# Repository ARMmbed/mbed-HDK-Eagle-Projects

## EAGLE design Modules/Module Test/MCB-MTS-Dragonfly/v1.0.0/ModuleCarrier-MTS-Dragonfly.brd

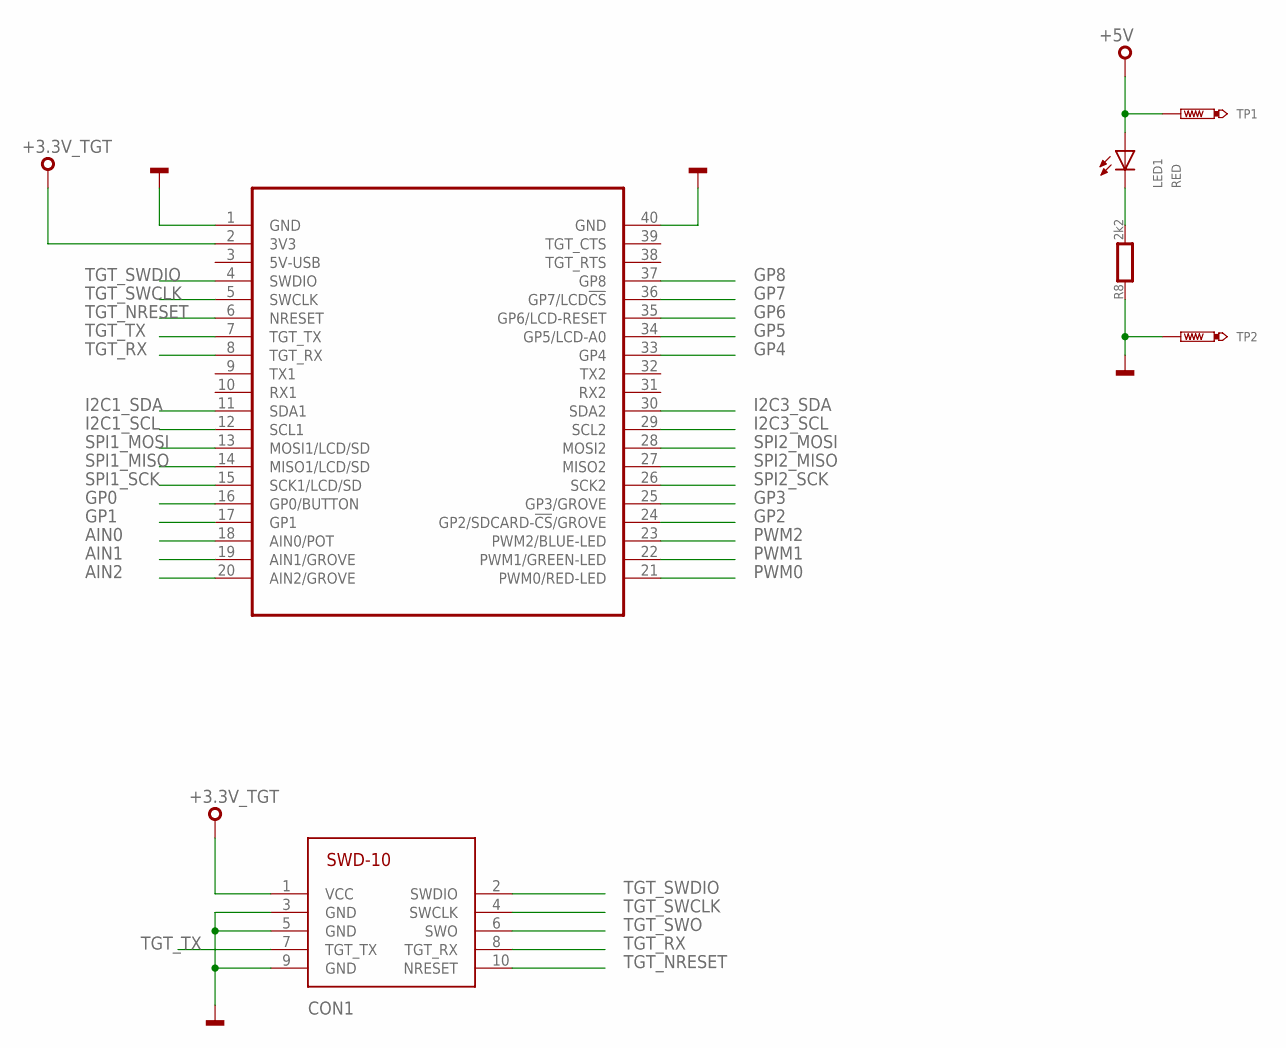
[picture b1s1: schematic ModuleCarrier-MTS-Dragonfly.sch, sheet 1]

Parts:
CON1: SWD-10/TC2050_SMD; FTSH-105-02
LED1: RED; CHIPLED_0603
MOD2: MODULE_DAUGHTER
R8: 2k2; 0603
TP1, TP2: TEST-POINT-50R-PTH; TP50-PTH

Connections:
+3.3V_TGT: CON1.1 (VCC), MOD2.2 (3V3)
+5V: LED1.A, TP1.TP; also elsewhere on the board
AIN0: MOD2.18 (AIN0/POT); also elsewhere on the board
AIN1: MOD2.19 (AIN1/GROVE); also elsewhere on the board
AIN2: MOD2.20 (AIN2/GROVE); also elsewhere on the board
GND: CON1.3 (GND), CON1.5 (GND), CON1.9 (GND), MOD2.1 (GND), MOD2.40 (GND), R8.1, TP2.TP; also elsewhere on the board
GP0: MOD2.16 (GP0/BUTTON); also elsewhere on the board
GP1: MOD2.17 (GP1); also elsewhere on the board
GP2: MOD2.24 (GP2/SDCARD-!CS!/GROVE); also elsewhere on the board
GP3: MOD2.25 (GP3/GROVE); also elsewhere on the board
GP4: MOD2.33 (GP4); also elsewhere on the board
GP5: MOD2.34 (GP5/LCD-A0); also elsewhere on the board
GP6: MOD2.35 (GP6/LCD-RESET); also elsewhere on the board
GP7: MOD2.36 (GP7/LCD!CS); also elsewhere on the board
GP8: MOD2.37 (GP8); also elsewhere on the board
I2C1_SCL: MOD2.12 (SCL1); also elsewhere on the board
I2C1_SDA: MOD2.11 (SDA1); also elsewhere on the board
I2C3_SCL: MOD2.29 (SCL2); also elsewhere on the board
I2C3_SDA: MOD2.30 (SDA2); also elsewhere on the board
PA_1: LED1.C, R8.2
PWM0: MOD2.21 (PWM0/RED-LED); also elsewhere on the board
PWM1: MOD2.22 (PWM1/GREEN-LED); also elsewhere on the board
PWM2: MOD2.23 (PWM2/BLUE-LED); also elsewhere on the board
SPI1_MISO: MOD2.14 (MISO1/LCD/SD); also elsewhere on the board
SPI1_MOSI: MOD2.13 (MOSI1/LCD/SD); also elsewhere on the board
SPI1_SCK: MOD2.15 (SCK1/LCD/SD); also elsewhere on the board
SPI2_MISO: MOD2.27 (MISO2); also elsewhere on the board
SPI2_MOSI: MOD2.28 (MOSI2); also elsewhere on the board
SPI2_SCK: MOD2.26 (SCK2); also elsewhere on the board
TGT_NRESET: CON1.10 (NRESET), MOD2.6 (NRESET); also elsewhere on the board
TGT_RX: CON1.8 (TGT_RX), MOD2.8 (TGT_RX); also elsewhere on the board
TGT_SWCLK: CON1.4 (SWCLK), MOD2.5 (SWCLK); also elsewhere on the board
TGT_SWDIO: CON1.2 (SWDIO), MOD2.4 (SWDIO); also elsewhere on the board
TGT_SWO: CON1.6 (SWO); also elsewhere on the board
TGT_TX: CON1.7 (TGT_TX), MOD2.7 (TGT_TX); also elsewhere on the board

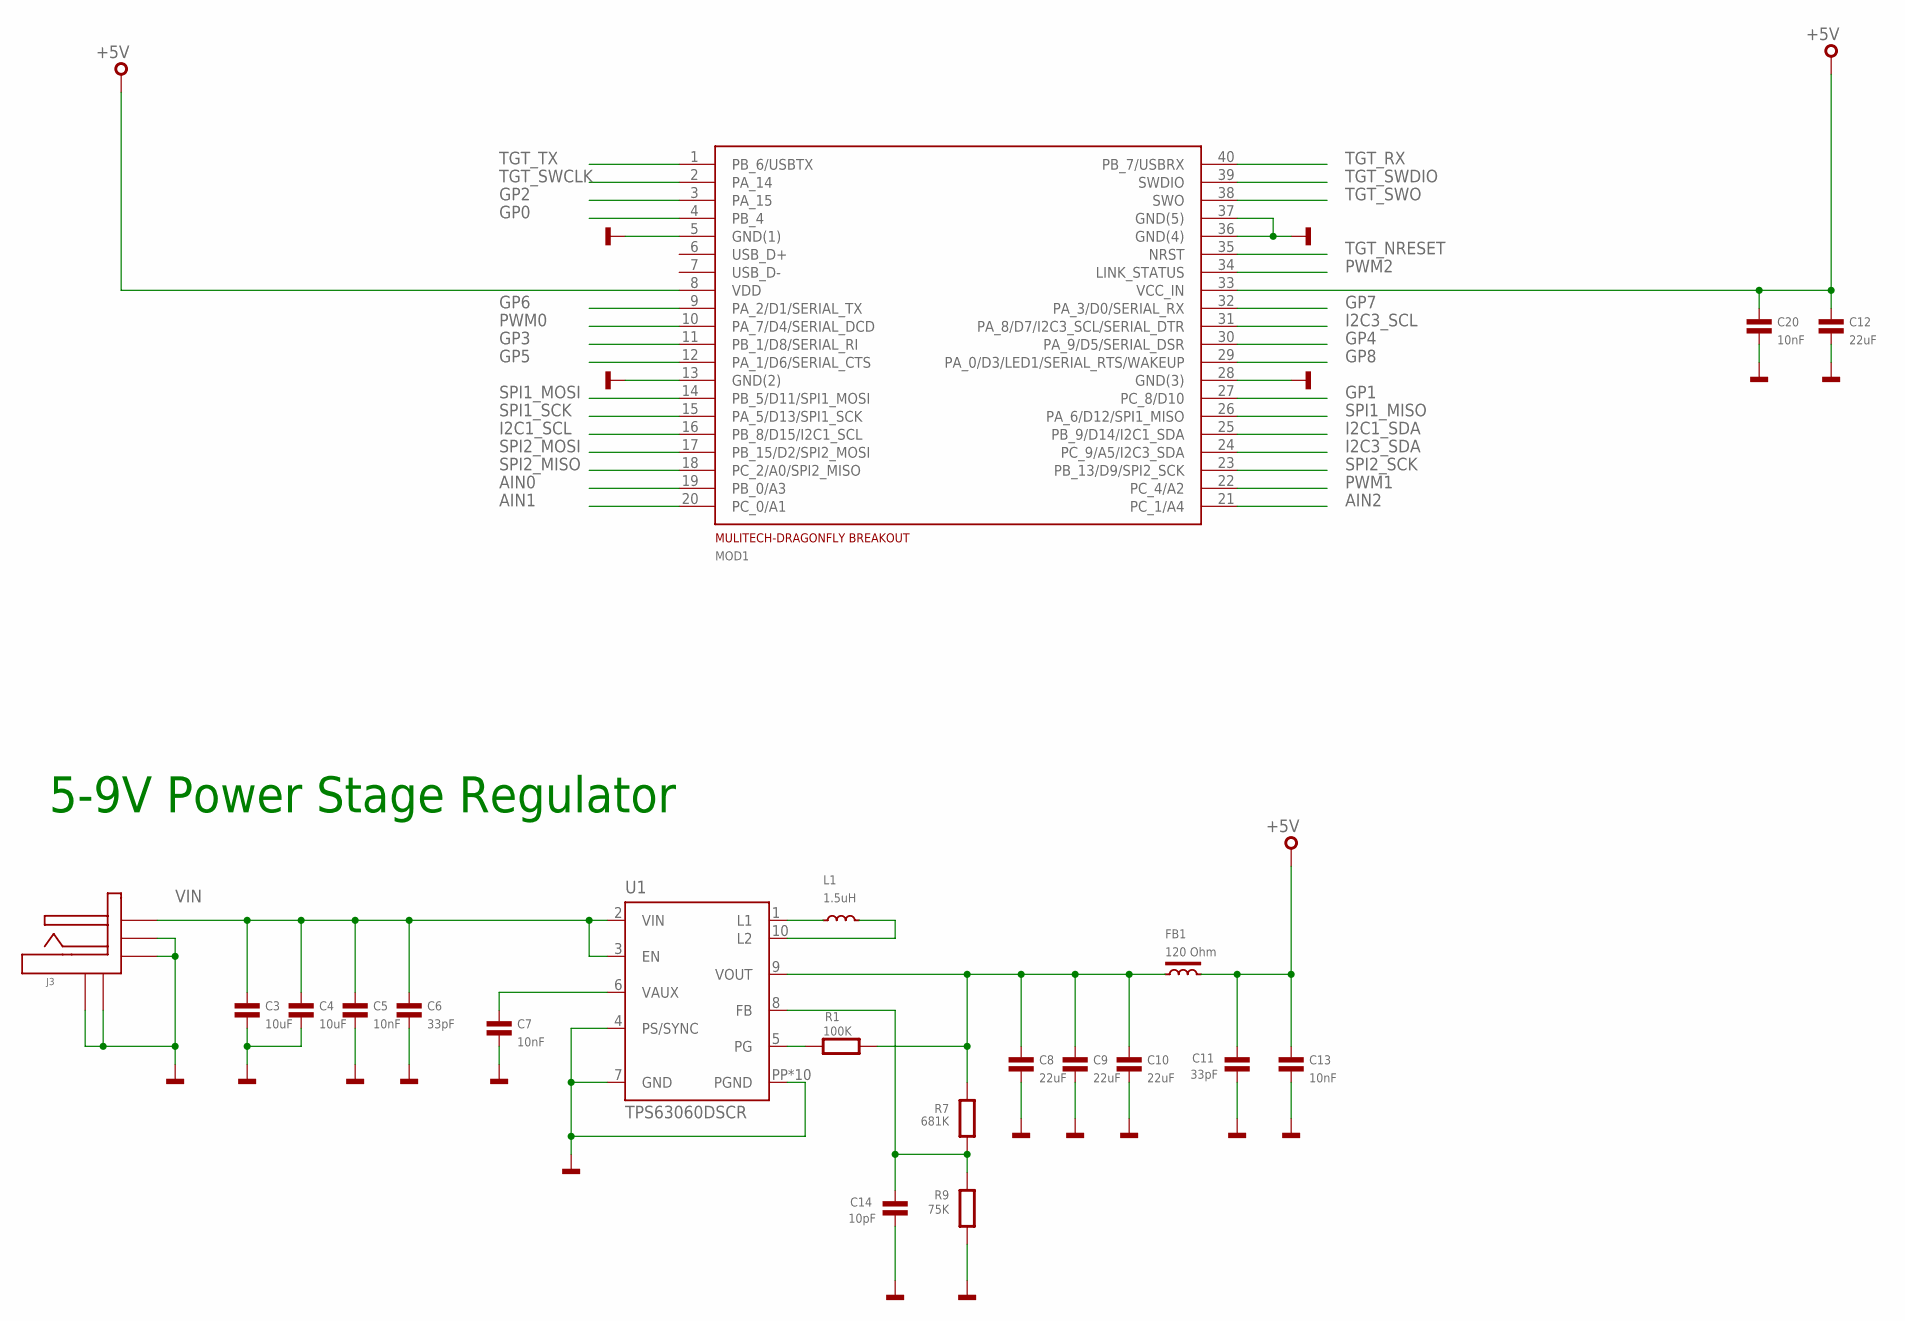
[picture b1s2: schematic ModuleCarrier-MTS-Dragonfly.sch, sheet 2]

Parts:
C3, C4: 10uF; 0603
C5, C7, C13, C20: 10nF; 0603
C6, C11: 33pF; 0603
C8, C9, C10, C12: 22uF; 0603
C14: 10pF; 0603
FB1: 120 Ohm; 0603
J3: FC68145S
L1: 1.5uH; XFL4020-472MEC
MOD1: MULITECH-DRAGONFLY-BREAKOUT
R1: 100K; 0402
R7: 681K; 0402
R9: 75K; 0402
U1: TPS63060DSCR; DSC-S-PWSON-N10

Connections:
+5V: C11.1, C12.1, C13.1, C20.1, FB1.2, MOD1.8 (VDD), MOD1.33 (VCC_IN); also elsewhere on the board
AIN0: MOD1.19 (PB_0/A3); also elsewhere on the board
AIN1: MOD1.20 (PC_0/A1); also elsewhere on the board
AIN2: MOD1.21 (PC_1/A4); also elsewhere on the board
GND: C3.2, C4.2, C5.2, C6.2, C7.2, C8.2, C9.2, C10.2, C11.2, C12.2, C13.2, C14.2, C20.2, J3.CASE1, J3.P$5 (CASE2), J3.SHUNT (SWITCHED), J3.SLEEVE, MOD1.5 (GND(1)), MOD1.13 (GND(2)), MOD1.28 (GND(3)), MOD1.36 (GND(4)), MOD1.37 (GND(5)), R9.1, U1.4 (PS/SYNC), U1.7 (GND), U1.PP (PGND), U1.PP@1 (PGND), U1.PP@2 (PGND), U1.PP@3 (PGND), U1.PP@4 (PGND), U1.PP@5 (PGND), U1.PP@7 (PGND), U1.PP@8 (PGND), U1.PP@9 (PGND), U1.PP@10 (PGND); also elsewhere on the board
GP0: MOD1.4 (PB_4); also elsewhere on the board
GP1: MOD1.27 (PC_8/D10); also elsewhere on the board
GP2: MOD1.3 (PA_15); also elsewhere on the board
GP3: MOD1.11 (PB_1/D8/SERIAL_RI); also elsewhere on the board
GP4: MOD1.30 (PA_9/D5/SERIAL_DSR); also elsewhere on the board
GP5: MOD1.12 (PA_1/D6/SERIAL_CTS); also elsewhere on the board
GP6: MOD1.9 (PA_2/D1/SERIAL_TX); also elsewhere on the board
GP7: MOD1.32 (PA_3/D0/SERIAL_RX); also elsewhere on the board
GP8: MOD1.29 (PA_0/D3/LED1/SERIAL_RTS/WAKEUP); also elsewhere on the board
I2C1_SCL: MOD1.16 (PB_8/D15/I2C1_SCL); also elsewhere on the board
I2C1_SDA: MOD1.25 (PB_9/D14/I2C1_SDA); also elsewhere on the board
I2C3_SCL: MOD1.31 (PA_8/D7/I2C3_SCL/SERIAL_DTR); also elsewhere on the board
I2C3_SDA: MOD1.24 (PC_9/A5/I2C3_SDA); also elsewhere on the board
unnamed: C7.1, U1.6 (VAUX)
unnamed: L1.P$1, U1.1 (L1)
unnamed: L1.P$2, U1.10 (L2)
unnamed: C14.1, R7.1, R9.2, U1.8 (FB)
unnamed: C8.1, C9.1, C10.1, FB1.1, R1.2, R7.2, U1.9 (VOUT)
unnamed: R1.1, U1.5 (PG)
PWM0: MOD1.10 (PA_7/D4/SERIAL_DCD); also elsewhere on the board
PWM1: MOD1.22 (PC_4/A2); also elsewhere on the board
PWM2: MOD1.34 (LINK_STATUS); also elsewhere on the board
SPI1_MISO: MOD1.26 (PA_6/D12/SPI1_MISO); also elsewhere on the board
SPI1_MOSI: MOD1.14 (PB_5/D11/SPI1_MOSI); also elsewhere on the board
SPI1_SCK: MOD1.15 (PA_5/D13/SPI1_SCK); also elsewhere on the board
SPI2_MISO: MOD1.18 (PC_2/A0/SPI2_MISO); also elsewhere on the board
SPI2_MOSI: MOD1.17 (PB_15/D2/SPI2_MOSI); also elsewhere on the board
SPI2_SCK: MOD1.23 (PB_13/D9/SPI2_SCK); also elsewhere on the board
TGT_NRESET: MOD1.35 (NRST); also elsewhere on the board
TGT_RX: MOD1.40 (PB_7/USBRX); also elsewhere on the board
TGT_SWCLK: MOD1.2 (PA_14); also elsewhere on the board
TGT_SWDIO: MOD1.39 (SWDIO); also elsewhere on the board
TGT_SWO: MOD1.38 (SWO); also elsewhere on the board
TGT_TX: MOD1.1 (PB_6/USBTX); also elsewhere on the board
VIN: C3.1, C4.1, C5.1, C6.1, J3.TIP, U1.2 (VIN), U1.3 (EN)

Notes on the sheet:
5-9V Power Stage Regulator

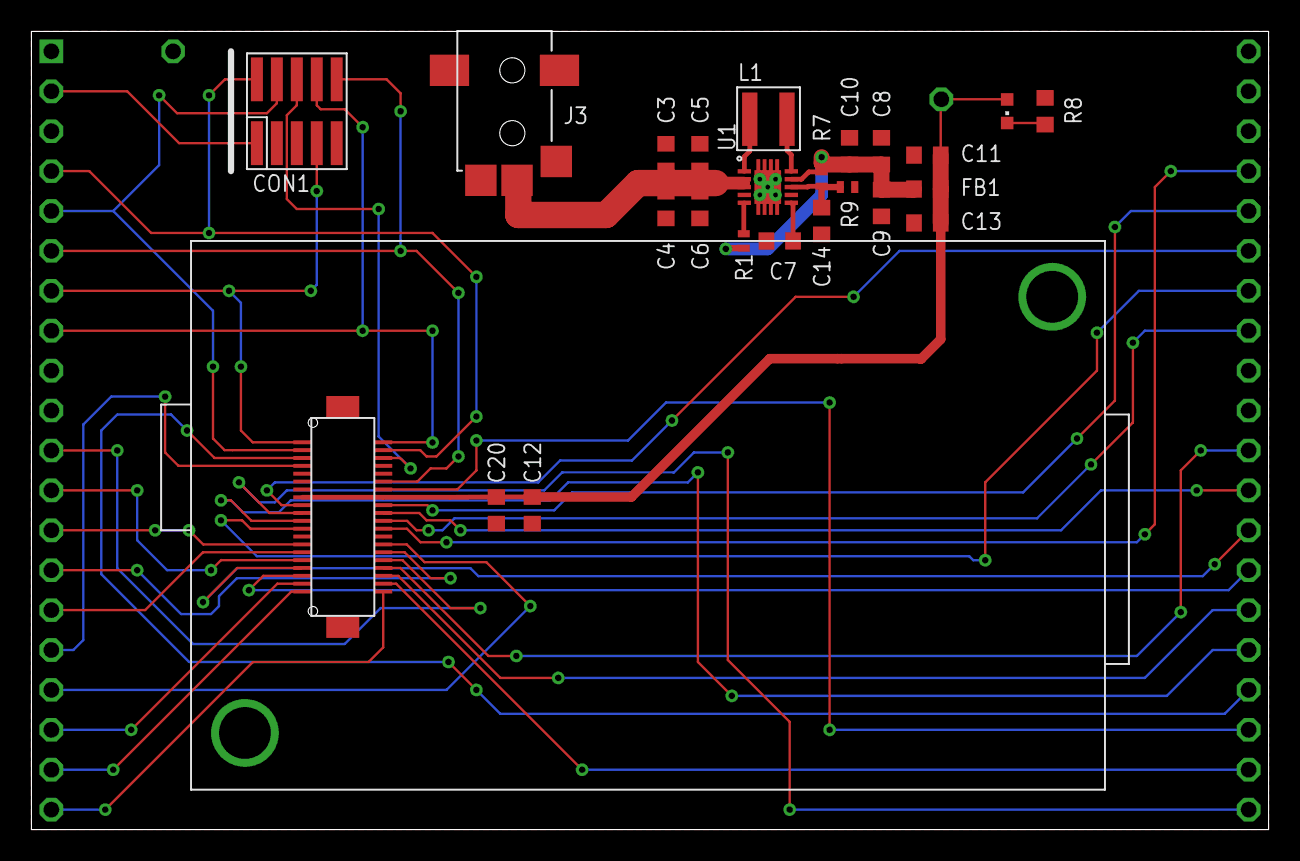
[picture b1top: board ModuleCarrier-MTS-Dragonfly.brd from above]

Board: 2 copper layers, 78.7 x 50.8 mm, 27 parts (0 on the bottom side), 42 nets.

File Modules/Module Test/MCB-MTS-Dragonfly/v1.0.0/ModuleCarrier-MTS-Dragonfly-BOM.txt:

Partlist exported from C:/Users/cstyles/Documents/mbed/Projects/blackbriar/ModuleCarrier-Multitech-Dragonfly/v1.0.0/ModuleCarrier-MTS-Dragonfly.sch at 22/11/2017 11:28

Qty Value                       Device                      Package                     Parts            Description                                                                                          MF                    MFN                     OC-DIGIKEY     OC-MOUSER           OC-NEWARK
1   1.5uH                       INDUCTORXFL4020             XFL4020-472MEC              L1               Inductor                                                                                                                                                                                       
1   100K                        RESISTOR0402                0402                        R1               Resistor                                                                                                                                                                                       
4   10nF                        CAPACITOR0603               0603                        C5, C7, C13, C20 Capacitor                                                                                                                                                                                      
1   10pF                        CAPACITOR0603               0603                        C14              Capacitor                                                                                                                                                                                      
2   10uF                        CAPACITOR0603               0603                        C3, C4           Capacitor                                                                                                                                                                                      
1   120 Ohm                     FERRITE0603                 0603                        FB1              Ferrite Bead                                                                                                                                                                                   
4   22uF                        CAPACITOR0603               0603                        C8, C9, C10, C12 Capacitor                                                                                                                                                                                      
1   2k2                         RESISTOR0603                0603                        R8               Resistor                                                                                                                                                                                       
2   33pF                        CAPACITOR0603               0603                        C6, C11          Capacitor                                                                                                                                                                                      
1   681K                        RESISTOR0402                0402                        R7               Resistor                                                                                                                                                                                       
1   75K                         RESISTOR0402                0402                        R9               Resistor                                                                                                                                                                                       
1   FC68145S                    FC68145S                    FC68145S                    J3               DC barrel socket                                                                                                                                                                                               
1   MULITECH-DRAGONFLY-BREAKOUT MULITECH-DRAGONFLY-BREAKOUT MULITECH-DRAGONFLY-BREAKOUT MOD1             Breakout for Multitech Dragonfly                                                                     Hirose                DF17(2.0)-40DP-0.5V(57) H11130CT-ND    798-DF172040DP05V57 2300341  
1   RED                         SMD_LED0603                 CHIPLED_0603                LED1             LED SMD, Colour Red                                                                                  Wurth Electronics Inc 150060RS75000           732-4978-1-ND  710-150060RS75000   2322071  
1   SWD-10/TC2050_SMD           SWD-10/TC2050_SMD           FTSH-105-02                 CON1             0.005" pitch 10-Pin Cortex Programming Header                                                                                            
1   TPS63060DSCR                TPS63060DSCR                DSC-S-PWSON-N10             U1               Buck Boost Conveter (2.5V-12Vin, 2.5V-8Vout, 2Aout)                                                  TEXAS INSTRUMENTS     TPS63060DSCR            296-30204-1-ND 595-TPS63060DSCR    76T8143

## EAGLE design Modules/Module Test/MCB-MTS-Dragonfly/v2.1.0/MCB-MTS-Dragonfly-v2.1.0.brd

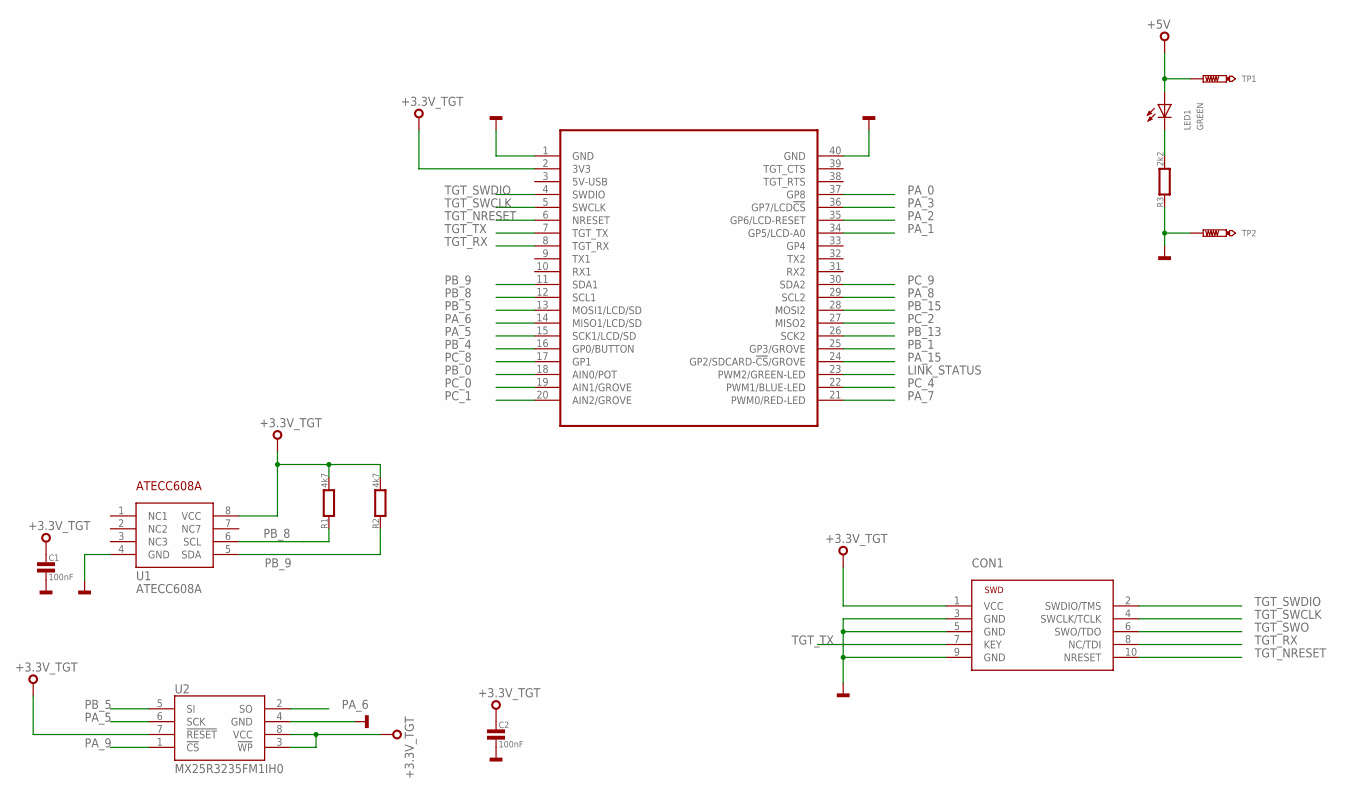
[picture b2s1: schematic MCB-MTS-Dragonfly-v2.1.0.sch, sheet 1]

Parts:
C1, C2: 100nF; 0603
CON1: SWD-10-SMD
LED1: GREEN; CHIPLED_0603
MOD1: MODULE_DAUGHTER
R1, R2: 4k7; 0603
R3: 2k2; 0603
TP1, TP2: TEST_POINT-50R-PTH; TP50-PTH
U1: ATECC608A; SO8
U2: MX25R3235FM1IH0; SO8

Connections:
+3.3V_TGT: C1.1, C2.1, CON1.1 (VCC), MOD1.2 (3V3), R1.2, R2.2, U1.8 (VCC), U2.3 (!WP), U2.7 (!RESET), U2.8 (VCC)
+5V: LED1.A, TP1.TP; also elsewhere on the board
GND: C1.2, C2.2, CON1.3 (GND), CON1.5 (GND), CON1.9 (GND), MOD1.1 (GND), MOD1.40 (GND), R3.1, TP2.TP, U1.4 (GND), U2.4 (GND); also elsewhere on the board
LINK_STATUS: MOD1.23 (PWM2/GREEN-LED); also elsewhere on the board
unnamed: LED1.C, R3.2
PA_0: MOD1.37 (GP8); also elsewhere on the board
PA_1: MOD1.34 (GP5/LCD-A0); also elsewhere on the board
PA_2: MOD1.35 (GP6/LCD-RESET); also elsewhere on the board
PA_3: MOD1.36 (GP7/LCD!CS); also elsewhere on the board
PA_5: MOD1.15 (SCK1/LCD/SD), U2.6 (SCK); also elsewhere on the board
PA_6: MOD1.14 (MISO1/LCD/SD), U2.2 (SO); also elsewhere on the board
PA_7: MOD1.21 (PWM0/RED-LED); also elsewhere on the board
PA_8: MOD1.29 (SCL2); also elsewhere on the board
PA_9: U2.1 (!CS); also elsewhere on the board
PA_15: MOD1.24 (GP2/SDCARD-!CS!/GROVE); also elsewhere on the board
PB_0: MOD1.18 (AIN0/POT); also elsewhere on the board
PB_1: MOD1.25 (GP3/GROVE); also elsewhere on the board
PB_4: MOD1.16 (GP0/BUTTON); also elsewhere on the board
PB_5: MOD1.13 (MOSI1/LCD/SD), U2.5 (SI); also elsewhere on the board
PB_8: MOD1.12 (SCL1), R1.1, U1.6 (SCL); also elsewhere on the board
PB_9: MOD1.11 (SDA1), R2.1, U1.5 (SDA); also elsewhere on the board
PB_13: MOD1.26 (SCK2); also elsewhere on the board
PB_15: MOD1.28 (MOSI2); also elsewhere on the board
PC_0: MOD1.19 (AIN1/GROVE); also elsewhere on the board
PC_1: MOD1.20 (AIN2/GROVE); also elsewhere on the board
PC_2: MOD1.27 (MISO2); also elsewhere on the board
PC_4: MOD1.22 (PWM1/BLUE-LED); also elsewhere on the board
PC_8: MOD1.17 (GP1); also elsewhere on the board
PC_9: MOD1.30 (SDA2); also elsewhere on the board
TGT_NRESET: CON1.10 (NRESET), MOD1.6 (NRESET); also elsewhere on the board
TGT_RX: CON1.8 (NC/TDI), MOD1.8 (TGT_RX); also elsewhere on the board
TGT_SWCLK: CON1.4 (SWCLK/TCLK), MOD1.5 (SWCLK); also elsewhere on the board
TGT_SWDIO: CON1.2 (SWDIO/TMS), MOD1.4 (SWDIO); also elsewhere on the board
TGT_SWO: CON1.6 (SWO/TDO); also elsewhere on the board
TGT_TX: CON1.7 (KEY), MOD1.7 (TGT_TX); also elsewhere on the board

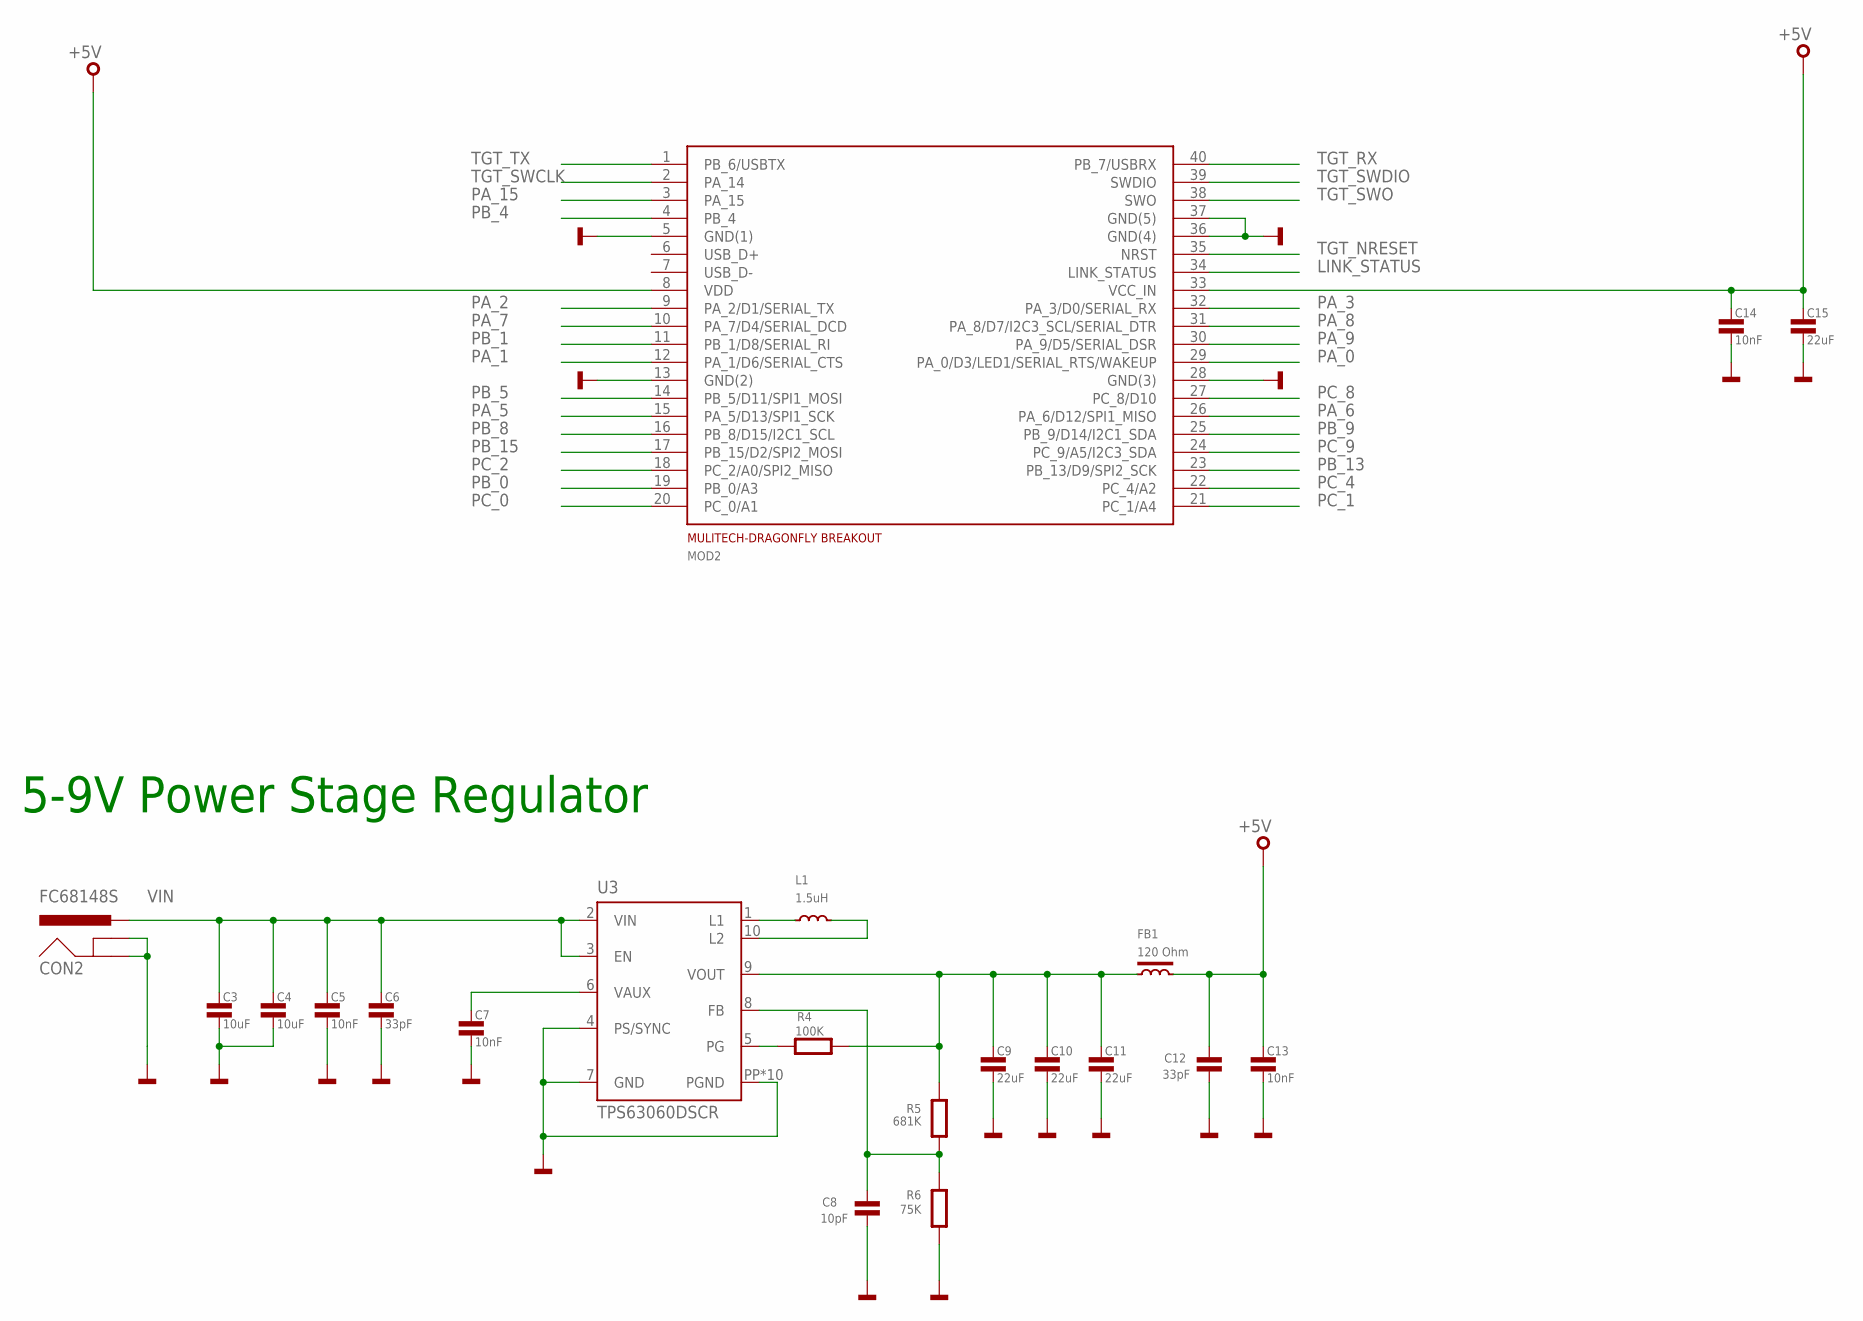
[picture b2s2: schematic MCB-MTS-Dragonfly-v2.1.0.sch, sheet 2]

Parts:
C3, C4: 10uF; 0603
C5, C7, C13, C14: 10nF; 0603
C6, C12: 33pF; 0603
C8: 10pF; 0603
C9, C10, C11, C15: 22uF; 0603
CON2: FC68148S
FB1: 120 Ohm; 0603
L1: 1.5uH; XFL4020-472MEC
MOD2: MULITECH-DRAGONFLY-BREAKOUT
R4: 100K; 0603
R5: 681K; 0603
R6: 75K; 0603
U3: TPS63060DSCR; DSC-S-PWSON-N10

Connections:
+5V: C12.1, C13.1, C14.1, C15.1, FB1.2, MOD2.8 (VDD), MOD2.33 (VCC_IN); also elsewhere on the board
GND: C3.2, C4.2, C5.2, C6.2, C7.2, C8.2, C9.2, C10.2, C11.2, C12.2, C13.2, C14.2, C15.2, CON2.2 (GNDBREAK), CON2.3 (GND), MOD2.5 (GND(1)), MOD2.13 (GND(2)), MOD2.28 (GND(3)), MOD2.36 (GND(4)), MOD2.37 (GND(5)), R6.1, U3.4 (PS/SYNC), U3.7 (GND), U3.PP (PGND), U3.PP@1 (PGND), U3.PP@2 (PGND), U3.PP@3 (PGND), U3.PP@4 (PGND), U3.PP@5 (PGND), U3.PP@7 (PGND), U3.PP@8 (PGND), U3.PP@9 (PGND), U3.PP@10 (PGND); also elsewhere on the board
LINK_STATUS: MOD2.34 (LINK_STATUS); also elsewhere on the board
unnamed: C7.1, U3.6 (VAUX)
unnamed: L1.P$1, U3.1 (L1)
unnamed: L1.P$2, U3.10 (L2)
unnamed: C8.1, R5.1, R6.2, U3.8 (FB)
unnamed: C9.1, C10.1, C11.1, FB1.1, R4.2, R5.2, U3.9 (VOUT)
unnamed: R4.1, U3.5 (PG)
PA_0: MOD2.29 (PA_0/D3/LED1/SERIAL_RTS/WAKEUP); also elsewhere on the board
PA_1: MOD2.12 (PA_1/D6/SERIAL_CTS); also elsewhere on the board
PA_2: MOD2.9 (PA_2/D1/SERIAL_TX); also elsewhere on the board
PA_3: MOD2.32 (PA_3/D0/SERIAL_RX); also elsewhere on the board
PA_5: MOD2.15 (PA_5/D13/SPI1_SCK); also elsewhere on the board
PA_6: MOD2.26 (PA_6/D12/SPI1_MISO); also elsewhere on the board
PA_7: MOD2.10 (PA_7/D4/SERIAL_DCD); also elsewhere on the board
PA_8: MOD2.31 (PA_8/D7/I2C3_SCL/SERIAL_DTR); also elsewhere on the board
PA_9: MOD2.30 (PA_9/D5/SERIAL_DSR); also elsewhere on the board
PA_15: MOD2.3 (PA_15); also elsewhere on the board
PB_0: MOD2.19 (PB_0/A3); also elsewhere on the board
PB_1: MOD2.11 (PB_1/D8/SERIAL_RI); also elsewhere on the board
PB_4: MOD2.4 (PB_4); also elsewhere on the board
PB_5: MOD2.14 (PB_5/D11/SPI1_MOSI); also elsewhere on the board
PB_8: MOD2.16 (PB_8/D15/I2C1_SCL); also elsewhere on the board
PB_9: MOD2.25 (PB_9/D14/I2C1_SDA); also elsewhere on the board
PB_13: MOD2.23 (PB_13/D9/SPI2_SCK); also elsewhere on the board
PB_15: MOD2.17 (PB_15/D2/SPI2_MOSI); also elsewhere on the board
PC_0: MOD2.20 (PC_0/A1); also elsewhere on the board
PC_1: MOD2.21 (PC_1/A4); also elsewhere on the board
PC_2: MOD2.18 (PC_2/A0/SPI2_MISO); also elsewhere on the board
PC_4: MOD2.22 (PC_4/A2); also elsewhere on the board
PC_8: MOD2.27 (PC_8/D10); also elsewhere on the board
PC_9: MOD2.24 (PC_9/A5/I2C3_SDA); also elsewhere on the board
TGT_NRESET: MOD2.35 (NRST); also elsewhere on the board
TGT_RX: MOD2.40 (PB_7/USBRX); also elsewhere on the board
TGT_SWCLK: MOD2.2 (PA_14); also elsewhere on the board
TGT_SWDIO: MOD2.39 (SWDIO); also elsewhere on the board
TGT_SWO: MOD2.38 (SWO); also elsewhere on the board
TGT_TX: MOD2.1 (PB_6/USBTX); also elsewhere on the board
VIN: C3.1, C4.1, C5.1, C6.1, CON2.1-1 (PWR), CON2.1-2 (PWR), U3.2 (VIN), U3.3 (EN)

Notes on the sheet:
5-9V Power Stage Regulator

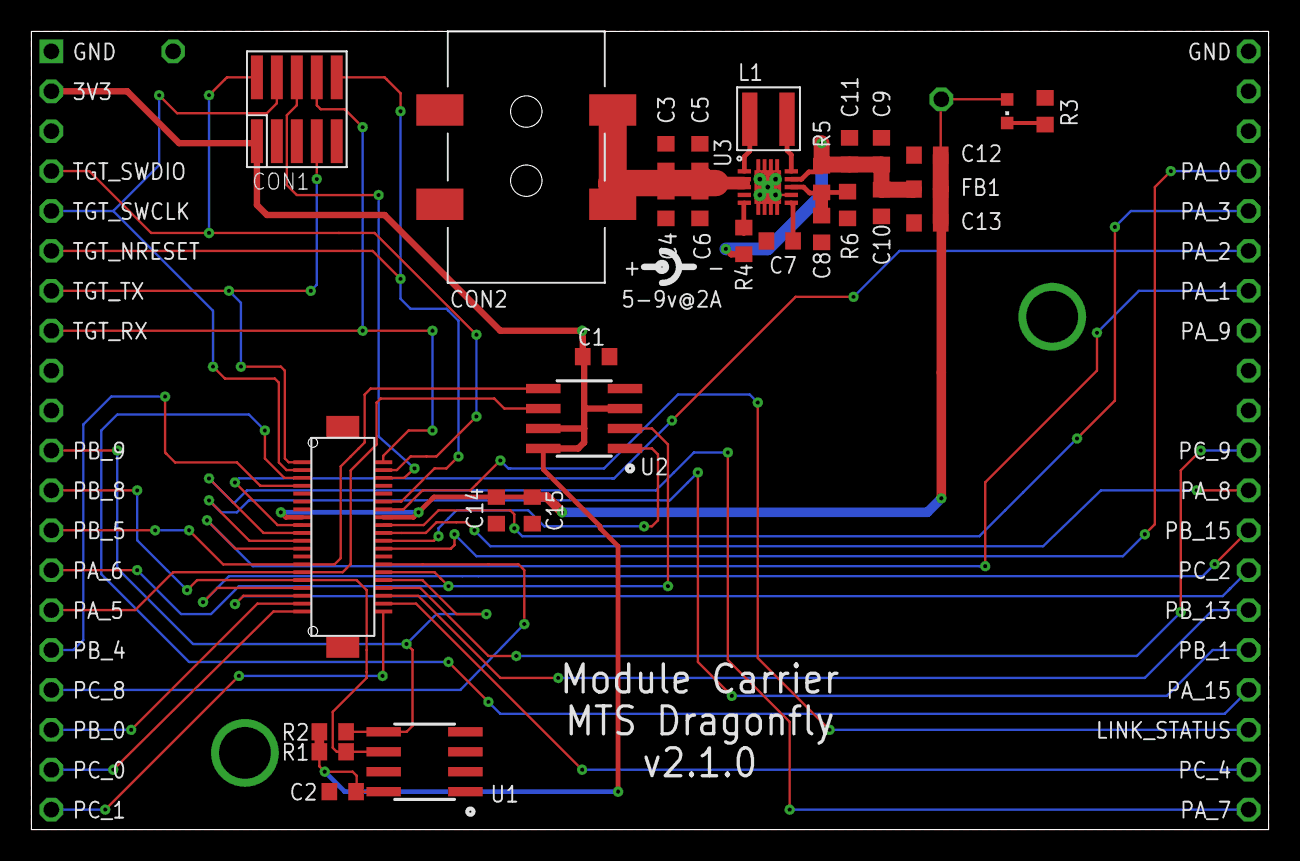
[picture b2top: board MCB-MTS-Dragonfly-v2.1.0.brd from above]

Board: 2 copper layers, 78.7 x 50.8 mm, 33 parts (0 on the bottom side), 42 nets.

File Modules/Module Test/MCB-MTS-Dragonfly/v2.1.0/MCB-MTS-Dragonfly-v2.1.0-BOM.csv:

"Qty";"Value";"Device";"Package";"Parts";"Description";"MF";"MFN";"OC-DIGIKEY";"OC-MOUSER";"OC-NEWARK";"OC_NEWARK";
"1";"1.5uH";"INDUCTORXFL4020";"XFL4020-472MEC";"L1";"Inductor";"CoilCraft";"XFL4020-472MEC";"";"";"2289218";"";
"1";"100K";"R0603";"0603";"R4";"Resistor";"";"";"";"";"";"";
"2";"100nF";"C0603";"0603";"C1, C2";"Capacitor";"";"";"";"";"";"";
"4";"10nF";"C0603";"0603";"C5, C7, C13, C14";"Capacitor";"";"";"";"";"";"";
"1";"10pF";"C0603";"0603";"C8";"Capacitor";"";"";"";"";"";"";
"2";"10uF";"C0603";"0603";"C3, C4";"Capacitor";"";"";"";"";"";"";
"1";"120 Ohm";"FB0603";"0603";"FB1";"Ferrite Bead";"";"";"";"";"";"";
"4";"22uF";"C0603";"0603";"C9, C10, C11, C15";"Capacitor";"";"";"";"";"";"";
"1";"2k2";"R0603";"0603";"R3";"Resistor";"";"";"";"";"";"";
"2";"33pF";"C0603";"0603";"C6, C12";"Capacitor";"";"";"";"";"";"";
"2";"4k7";"R0603";"0603";"R1, R2";"Resistor";"";"";"";"";"";"";
"1";"681K";"R0603";"0603";"R5";"Resistor";"";"";"";"";"";"";
"1";"75K";"R0603";"0603";"R6";"Resistor";"";"";"";"";"";"";
"1";"ATECC608A";"ATECC608A";"SO8";"U1";"I2C Secure element and crytpo accelerator";"Atmel";"ATECC608A";"ATECC608A-SSHDA-TCT-ND ";"556-ATECC608ASSHDAB ";"";"";
"1";"FC68148S";"FC68148S";"FC68148S";"CON2";"Power Jack";"Cliff";"FC68148S";"";"";"";"1889309";
"1";"GREEN";"SMD_LED0603";"CHIPLED_0603";"LED1";"LED SMD, Colour Red";"Wurth Electronics Inc";"150060RS75000";"732-4978-1-ND";"710-150060RS75000";"2322071";"";
"1";"MODULE_DAUGHTER";"MODULE_DAUGHTER";"MODULE_DAUGHTER";"MOD1";"";"";"";"";"";"";"";
"1";"MULITECH-DRAGONFLY-BREAKOUT";"MULITECH-DRAGONFLY-BREAKOUT";"MULITECH-DRAGONFLY-BREAKOUT";"MOD2";"Breakout for Multitech Dragonfly";"Hirose";"DF17(2.0)-40DP-0.5V(57)";"H11130CT-ND";"798-DF172040DP05V57";"2300341";"";
"1";"MX25R3235FM1IH0";"MX25R3235FM1IH0";"SO8";"U2";"Serial Flash 32 Mb 80 Mhz";"Macronix";"MX25R3235FM1IH0";"1092-1175-ND";"";"";"";
"1";"SWD-10/TC2050_SMD";"SWD-10/TC2050_SMD";"FTSH-105-02";"CON1";"1mm pitch 10-Pin Cortex Programming Header with optional TC2050 footprint solderless interchangeable";"";"";"";"";"";"";
"2";"TEST_POINT-50R-PTH";"TEST_POINT-50R-PTH";"TP50-PTH";"TP1, TP2";"";"";"";"";"";"";"";
"1";"TPS63060DSCR";"TPS63060DSCR";"DSC-S-PWSON-N10";"U3";"Buck Boost Conveter (2.5V-12Vin, 2.5V-8Vout, 2Aout)";"TEXAS INSTRUMENTS";"TPS63060DSCR";"296-30204-1-ND";"595-TPS63060DSCR";"76T8143";"";
